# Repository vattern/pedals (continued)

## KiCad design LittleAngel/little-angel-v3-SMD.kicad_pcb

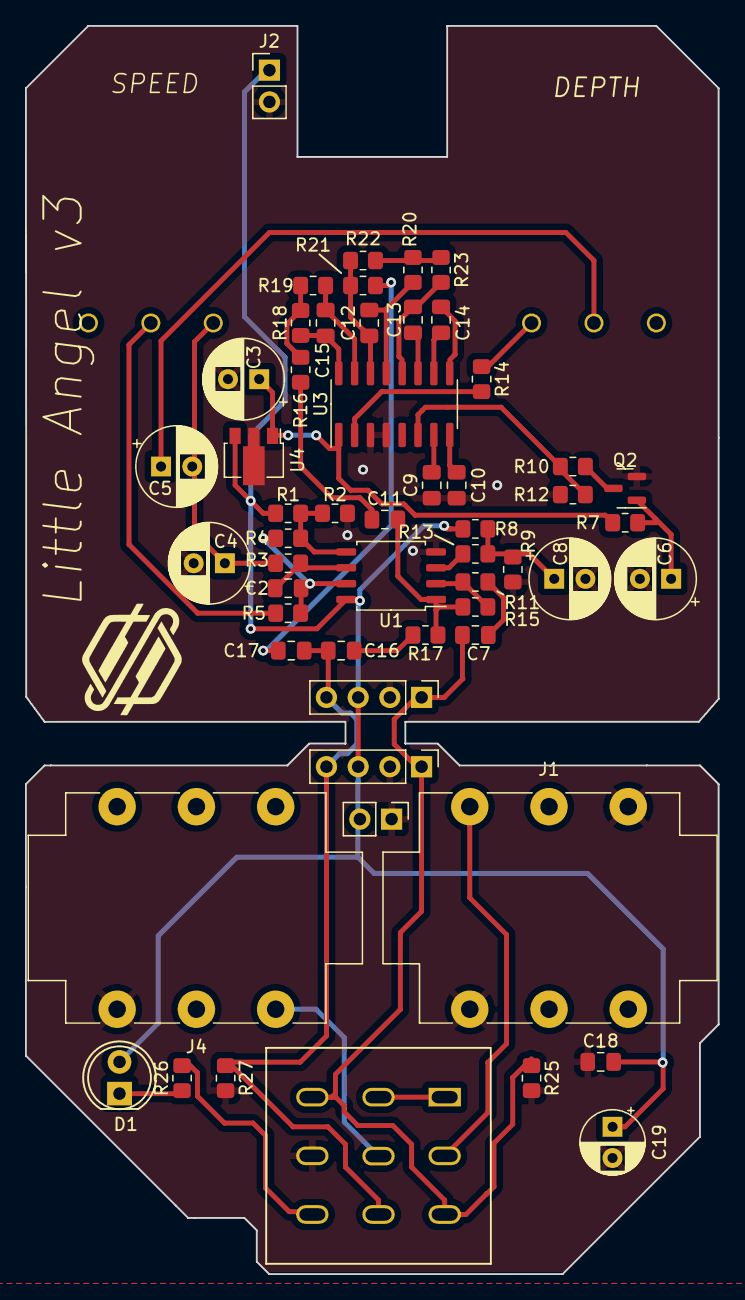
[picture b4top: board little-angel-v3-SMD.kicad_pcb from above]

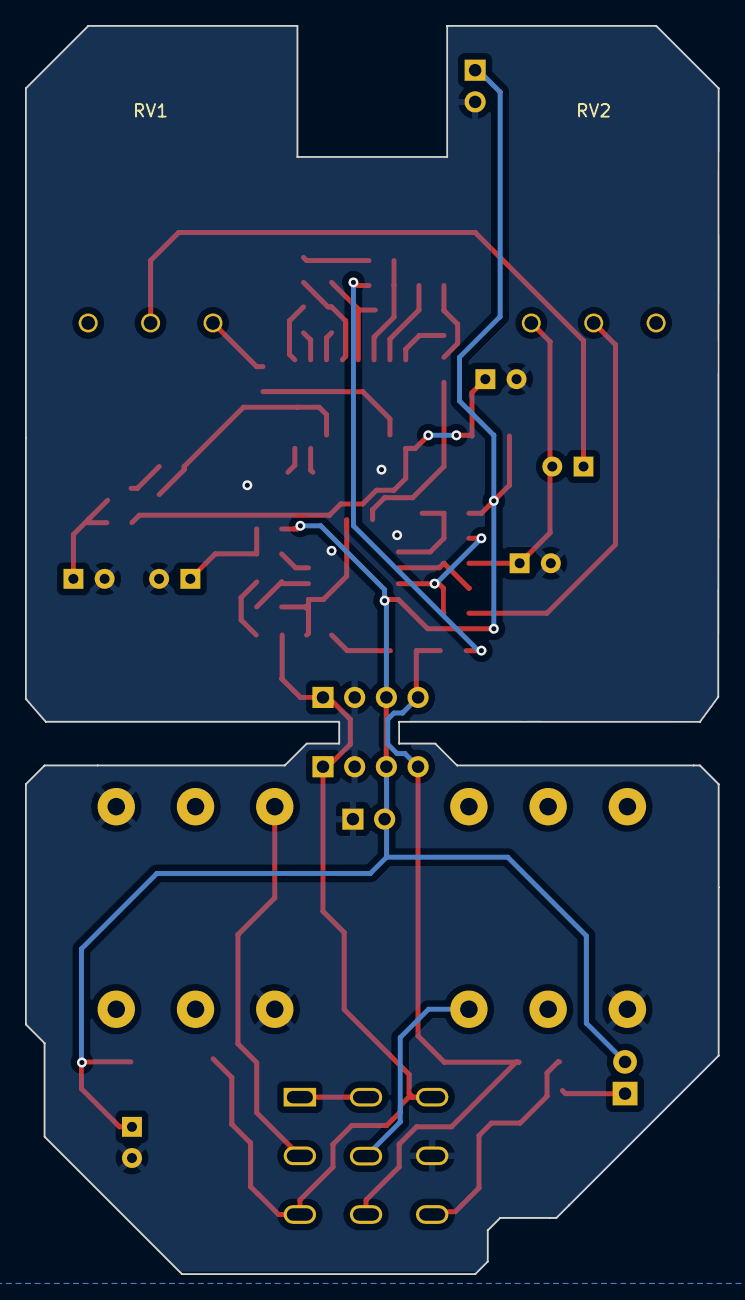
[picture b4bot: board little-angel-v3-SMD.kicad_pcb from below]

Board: 2 copper layers, 55.5 x 100.0 mm, 58 parts (2 on the bottom side), 41 nets.

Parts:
C2: 10nF; C_0805_2012Metric_Pad1.18x1.45mm_HandSolder
C3, C6, C8: 47uF; CP_Radial_D6.3mm_P2.50mm
C4, C5: 10uF; CP_Radial_D6.3mm_P2.50mm
C7, C9, C10, C11, C16, C17, C18: 100nF; C_0805_2012Metric_Pad1.18x1.45mm_HandSolder
C12: 10n; C_0805_2012Metric_Pad1.18x1.45mm_HandSolder
C13, C14: 100n; C_0805_2012Metric_Pad1.18x1.45mm_HandSolder
C15: 3n3; C_0805_2012Metric_Pad1.18x1.45mm_HandSolder
C19: 100uF; CP_Radial_D5.0mm_P2.50mm
D1: LED; LED-5MM
J1, J4: NMJ6HCD2; Jack_6.35mm_Neutrik_NMJ6HCD2_Horizontal
J2, J3: V+ GND; PinHeader_1x02_P2.54mm_Vertical
JOVGI1, JOVGI2: OVGI; Pin_Header_Straight_1x04_Pitch2.54mm
N1: Housing; 1590B
Q2: MMBT3904; SOT-23
R1: 100k; R_0805_2012Metric_Pad1.20x1.40mm_HandSolder
R2: 47k; R_0805_2012Metric_Pad1.20x1.40mm_HandSolder
R3: 220K; R_0805_2012Metric_Pad1.20x1.40mm_HandSolder
R4: 220k; R_0805_2012Metric_Pad1.20x1.40mm_HandSolder
R5: 4k7; R_0805_2012Metric_Pad1.20x1.40mm_HandSolder
R7: 68K; R_0805_2012Metric_Pad1.20x1.40mm_HandSolder
R8, R9, R16, R17, R18, R19, R20, R21, R22, R23: 10k; R_0805_2012Metric_Pad1.20x1.40mm_HandSolder
R10: 100R; R_0805_2012Metric_Pad1.20x1.40mm_HandSolder
R11: 470k; R_0805_2012Metric_Pad1.20x1.40mm_HandSolder
R12: 2k2; R_0805_2012Metric_Pad1.20x1.40mm_HandSolder
R13: 330k; R_0805_2012Metric_Pad1.20x1.40mm_HandSolder
R14: 33k; R_0805_2012Metric_Pad1.20x1.40mm_HandSolder
R15, R25: 1M; R_0805_2012Metric_Pad1.20x1.40mm_HandSolder
R26: 1K; R_0805_2012Metric_Pad1.20x1.40mm_HandSolder
R27: 100K; R_0805_2012Metric_Pad1.20x1.40mm_HandSolder
RV1: 470K lin; Potentiometer_ALPHA_RV16106N
RV2: 100k lin; Potentiometer_ALPHA_RV16106N
SW1: SW_3PDT; 3PDT-Footswitch
U1: NE5532; SOIC-8_5.275x5.275mm_P1.27mm
U3: PT2399; SOIC-16_3.9x9.9mm_P1.27mm
U4: MC78L05_SOT89; SOT-89-3

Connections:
+5V: C3.1, R7.2, U3.1 (VCC), U4.1 (OUT)
+9V: C18.2, C19.1, D1.2 (A), J2.1, J3.2, JOVGI1.3, JOVGI2.3, R1.2, R8.2, U1.8 (V+), U4.3 (IN)
GND: C3.2, C4.2, C6.2, C8.2, C9.1, C10.1, C18.1, C19.2, J1.S, J1.TN, J2.2, J3.1, J4.S, JOVGI1.2, JOVGI2.2, Q2.2 (E), R2.1, R9.1, R12.1, R25.2, R27.2, SW1.6 (B), U1.4 (V-), U3.3 (AGND), U3.4 (DGND), U4.2 (GND)
I: C7.1, JOVGI1.1, JOVGI2.1, R25.1, SW1.3 (A), SW1.7 (C)
unnamed: C2.2, R4.2, R5.1, U1.7
unnamed: C4.1, C5.2, R3.2, RV2.1
unnamed: C5.1, RV1.2
unnamed: C7.2, R11.1
unnamed: C8.1, R8.1, R9.2, R13.1
unnamed: C11.1, R16.1
unnamed: C11.2, R15.2, R17.1, U1.1
unnamed: C16.1, R17.2
unnamed: C17.1, R21.2
unnamed: D1.1 (K), R26.1
unnamed: C6.1, Q2.1 (B), R7.1
unnamed: Q2.3 (C), R10.1
unnamed: R5.2, RV2.2
unnamed: R14.1, RV1.3
unnamed: R16.2, R18.2, R19.2
unnamed: R20.1, R22.1, R23.1
unnamed: SW1.1 (A), SW1.2 (A)
unnamed: J1.T, SW1.4 (B)
unnamed: J4.T, SW1.5 (B)
unnamed: R26.2, SW1.9 (C)
unnamed: R13.2, U1.3 (+)
unnamed: R11.2, R15.1, U1.2 (-)
unnamed: R1.1, R2.2, R4.1, U1.5 (+)
unnamed: C2.1, R3.1, U1.6 (-)
unnamed: C10.2, U3.8 (CC0)
unnamed: C9.2, U3.7 (CC1)
unnamed: C15.1, R18.1, U3.16 (LPF1-IN)
unnamed: C15.2, R19.1, U3.15 (LPF1-OUT)
unnamed: C12.2, R20.2, U3.13 (LPF2-IN)
unnamed: C12.1, R21.1, R22.2, U3.14 (LPF2-OUT)
unnamed: C14.1, U3.10 (OP1-IN)
unnamed: C14.2, U3.9 (OP1-OUT)
unnamed: C13.2, U3.11 (OP2-IN)
unnamed: C13.1, R23.2, U3.12 (OP2-OUT)
unnamed: R14.2, U3.2 (REF)
unnamed: R10.2, R12.2, U3.6 (VCO)
O: C16.2, C17.2, JOVGI1.4, JOVGI2.4, R27.1, SW1.8 (C)

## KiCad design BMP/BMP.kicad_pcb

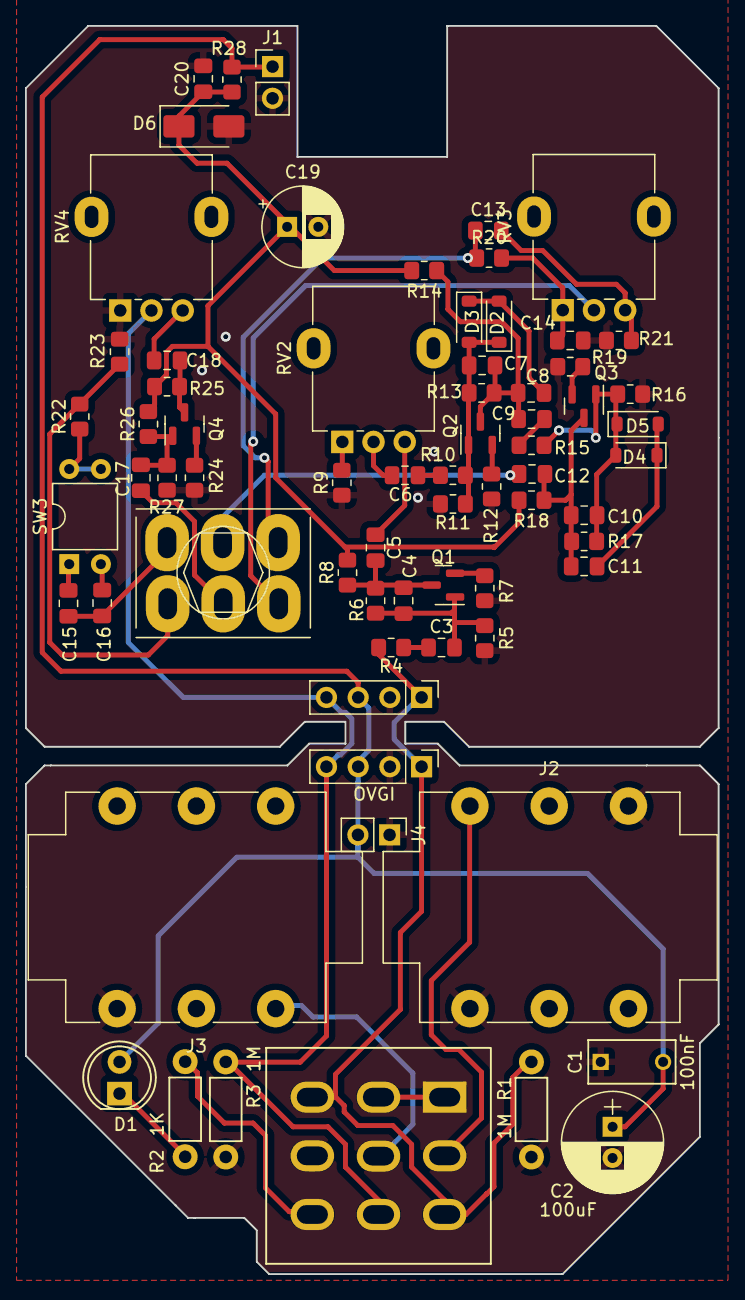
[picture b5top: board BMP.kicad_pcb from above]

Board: 2 copper layers, 55.5 x 100.0 mm, 71 parts (0 on the bottom side), 42 nets.

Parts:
C1: 100nF; C_Rect_L7_W3.5_P5
C2: 100uF; CP_Radial_D8.0mm_P2.50mm
C3, C5, C6, C8, C9, C11, C12, C17, C18, C20: 100n; C_0805_2012Metric_Pad1.18x1.45mm_HandSolder
C4, C7, C10: 470p; C_0805_2012Metric_Pad1.18x1.45mm_HandSolder
C13: 3n9; C_0805_2012Metric_Pad1.18x1.45mm_HandSolder
C14, C16: 10n; C_0805_2012Metric_Pad1.18x1.45mm_HandSolder
C15: 4n7; C_0805_2012Metric_Pad1.18x1.45mm_HandSolder
C19: 100u; CP_Radial_D6.3mm_P2.50mm
D1: LED; LED-5MM
D2, D3, D4, D5: 1N4148W; D_SOD-123
D6: US1G; D_SMA
J1, J4: V+ GND; PinHeader_1x02_P2.54mm_Vertical
J2, J3: NMJ6HCD2; Jack_6.35mm_Neutrik_NMJ6HCD2_Horizontal
JOVGI1, JOVGI2: OVGI; Pin_Header_Straight_1x04_Pitch2.54mm
N1: Housing; 1590B
Q1, Q2, Q3, Q4: BC849; SOT-23
R1, R3: 1M; Resistor_Horizontal_RM7mm
R2: 1K; Resistor_Horizontal_RM7mm
R4, R20, R21: 33k; R_0805_2012Metric_Pad1.20x1.40mm_HandSolder
R5, R11, R16, R27: 100k; R_0805_2012Metric_Pad1.20x1.40mm_HandSolder
R6, R13, R17, R26: 470k; R_0805_2012Metric_Pad1.20x1.40mm_HandSolder
R7, R12, R19, R28: 100R; R_0805_2012Metric_Pad1.20x1.40mm_HandSolder
R8, R14, R18, R25: 12k; R_0805_2012Metric_Pad1.20x1.40mm_HandSolder
R9: 560R; R_0805_2012Metric_Pad1.20x1.40mm_HandSolder
R10, R15: 8k2; R_0805_2012Metric_Pad1.20x1.40mm_HandSolder
R22, R23: 47k; R_0805_2012Metric_Pad1.20x1.40mm_HandSolder
R24: 2k7; R_0805_2012Metric_Pad1.20x1.40mm_HandSolder
RV2, RV3, RV4: 100kB; Potentiometer_Alpha_RD901F-40-00D_Single_Vertical
SW1: SW_3PDT; 3PDT-Footswitch
SW2: SW_DPDT_x2; SW_Toggle_Blue_wSlots_1
SW3: SW_DIP_x02; DIP-4_W7.62mm

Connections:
+9V: C1.2, C2.1, D1.2 (A), J1.1, J4.2, JOVGI1.3, JOVGI2.3, R28.1
A: C12.2, SW2.2 (B)
GND: C1.1, C2.2, C14.1, C19.2, C20.1, D6.2 (A), J1.2, J2.S, J2.TN, J3.S, J4.1, JOVGI1.2, JOVGI2.2, R1.2, R3.2, R5.1, R7.1, R9.1, R11.1, R12.1, R16.1, R19.1, R21.1, R23.1, R24.1, R27.1, RV4.1, SW1.6 (B)
I: JOVGI1.1, JOVGI2.1, R1.1, R4.1, SW1.3 (A), SW1.7 (C)
unnamed: C3.1, R4.2
unnamed: C5.2, RV2.3
unnamed: C6.1, RV2.2
unnamed: C6.2, R10.1
unnamed: C9.2, R15.1
unnamed: C13.2, R21.2, RV3.3
unnamed: C14.2, R20.2, RV3.1
unnamed: C15.2, SW3.1
unnamed: C16.2, SW3.2
unnamed: C18.1, RV4.3
unnamed: D1.1 (K), R2.1
unnamed: C8.1, D2.2 (A), D3.1 (K)
unnamed: C7.1, D2.1 (K), D3.2 (A), Q2.1 (B), R10.2, R11.2, R13.1
unnamed: C10.1, D4.2 (A), D5.1 (K), Q3.1 (B), R15.2, R16.2, R17.1
unnamed: C11.1, D4.1 (K), D5.2 (A)
unnamed: C3.2, C4.1, Q1.1 (B), R5.2, R6.1
unnamed: C4.2, C5.1, Q1.3 (C), R6.2, R8.1
unnamed: Q1.2 (E), R7.2
unnamed: C7.2, C8.2, C9.1, Q2.3 (C), R13.2, R14.1
unnamed: Q2.2 (E), R12.2
unnamed: C10.2, C11.2, C12.1, Q3.3 (C), R17.2, R18.1
unnamed: Q3.2 (E), R19.2
unnamed: C17.1, Q4.1 (B), R26.1, R27.2
unnamed: C18.2, Q4.3 (C), R25.1
unnamed: Q4.2 (E), R24.2
unnamed: R9.2, RV2.1
unnamed: R22.1, SW3.3, SW3.4
unnamed: SW1.1 (A), SW1.2 (A)
unnamed: J2.T, SW1.4 (B)
unnamed: J3.T, SW1.5 (B)
unnamed: R2.2, SW1.9 (C)
unnamed: C15.1, C16.1, SW2.1 (A)
unnamed: C13.1, R20.1, SW2.3 (C)
unnamed: R22.2, R23.2, SW2.4 (A)
unnamed: C17.2, SW2.5 (B)
unnamed: RV3.2, SW2.6 (C)
O: JOVGI1.4, JOVGI2.4, R3.1, RV4.2, SW1.8 (C)
VP: C19.1, C20.2, D6.1 (K), R8.2, R14.2, R18.2, R25.2, R26.2, R28.2

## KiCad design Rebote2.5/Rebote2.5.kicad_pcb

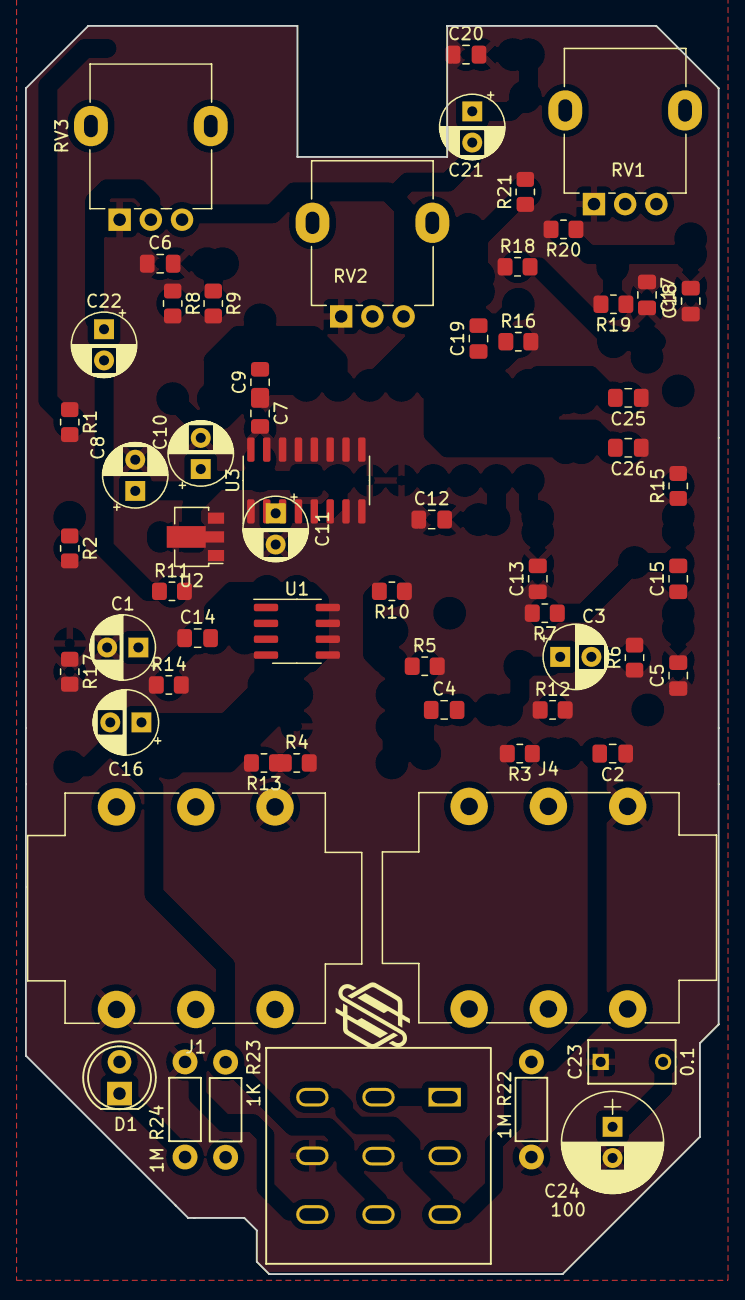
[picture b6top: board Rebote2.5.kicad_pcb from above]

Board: 2 copper layers, 55.5 x 100.0 mm, 61 parts (0 on the bottom side), 42 nets, no tracks yet.

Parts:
C1, C8, C10, C11: 47uF; CP_Radial_D5.0mm_P2.50mm
C2: 8n2; C_0805_2012Metric_Pad1.18x1.45mm_HandSolder
C3, C16, C21, C22: 1uF; CP_Radial_D5.0mm_P2.50mm
C4: 5pF; C_0805_2012Metric_Pad1.18x1.45mm_HandSolder
C5: 27nF; C_0805_2012Metric_Pad1.18x1.45mm_HandSolder
C6, C17, C18: 10nF; C_0805_2012Metric_Pad1.18x1.45mm_HandSolder
C7, C12, C13, C15, C20: 100nF; C_0805_2012Metric_Pad1.18x1.45mm_HandSolder
C9: 560pF; C_0805_2012Metric_Pad1.18x1.45mm_HandSolder
C14: 51pF; C_0805_2012Metric_Pad1.18x1.45mm_HandSolder
C19: 1nF; C_0805_2012Metric_Pad1.18x1.45mm_HandSolder
C23: 0.1; C_Rect_L7_W3.5_P5
C24: 100; CP_Radial_D8.0mm_P2.50mm
C25, C26: 82nF; C_0805_2012Metric_Pad1.18x1.45mm_HandSolder
D1: LED; LED-5MM
J1, J4: NMJ6HCD2; Jack_6.35mm_Neutrik_NMJ6HCD2_Horizontal
N1: Housing; 1590B
R1, R2, R6, R7, R8, R16, R18, R19: 12K; R_0805_2012Metric_Pad1.20x1.40mm_HandSolder
R3, R4, R5: 510K; R_0805_2012Metric_Pad1.20x1.40mm_HandSolder
R9: 47K; R_0805_2012Metric_Pad1.20x1.40mm_HandSolder
R10, R14, R20: 24K; R_0805_2012Metric_Pad1.20x1.40mm_HandSolder
R11: 33K; R_0805_2012Metric_Pad1.20x1.40mm_HandSolder
R12, R13: 1k; R_0805_2012Metric_Pad1.20x1.40mm_HandSolder
R15: 15K; R_0805_2012Metric_Pad1.20x1.40mm_HandSolder
R17: 100K; R_0805_2012Metric_Pad1.20x1.40mm_HandSolder
R21: 2k7; R_0805_2012Metric_Pad1.20x1.40mm_HandSolder
R22, R24: 1M; Resistor_Horizontal_RM7mm
R23: 1K; Resistor_Horizontal_RM7mm
RV1: 50KB; Potentiometer_Alpha_RD901F-40-00D_Single_Vertical
RV2: 25KB; Potentiometer_Alpha_RD901F-40-00D_Single_Vertical
RV3: 100KB; Potentiometer_Alpha_RD901F-40-00D_Single_Vertical
SW1: SW_3PDT; 3PDT-Footswitch
U1: TL072; SOIC-8_3.9x4.9mm_P1.27mm
U2: L78L05_SOT89; SOT-89-3
U3: PT2399; SOIC-16_3.9x9.9mm_P1.27mm

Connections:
+5V: C7.2, C8.1, C10.1, U2.1 (OUT), U3.1 (VCC)
+9V: C23.2, C24.1, D1.2 (A), R1.1, U1.8 (V+), U2.3 (IN)
AI: C3.1, C4.2, R5.2, R10.1, U1.7
DELAY_OUT: C26.2, R16.1, U3.12 (OP2-OUT)
GND: C1.2, C5.1, C6.1, C7.1, C8.2, C10.2, C11.2, C12.1, C13.1, C17.1, C18.1, C20.1, C23.1, C24.2, J1.S, J1.TN, J4.S, R2.2, R17.1, R22.2, R24.2, RV1.1, RV2.1, RV3.1, SW1.6 (B), U1.4 (V-), U2.2 (GND), U3.3 (AGND), U3.4 (DGND)
I: C2.1, R22.1, SW1.3 (A), SW1.7 (C)
LPF1-IN: C9.1, R8.2, U3.16 (LPF1-IN)
LPF1-OUT: C9.2, R9.2, U3.15 (LPF1-OUT)
LPF2-IN: C19.1, R19.2, U3.13 (LPF2-IN)
LPF2-OUT: C19.2, R20.2, R21.1, U3.14 (LPF2-OUT)
unnamed: C2.2, R3.1
unnamed: C3.2, R6.1
unnamed: C6.2, R7.2, R8.1, R9.1
unnamed: C14.2, C16.1, R14.2, U1.1
unnamed: C5.2, C15.1, R6.2, R7.1
unnamed: C15.2, R15.1
unnamed: C17.2, R16.2, R18.1
unnamed: C18.2, R18.2, R19.1, R20.1
unnamed: C20.2, C21.1, R21.2
unnamed: C21.2, RV2.3, RV3.3
unnamed: C22.1, RV3.2
unnamed: C22.2, R11.1
unnamed: D1.1 (K), R23.1
unnamed: R12.2, RV1.2, RV1.3
unnamed: R15.2, RV2.2
unnamed: SW1.1 (A), SW1.2 (A)
unnamed: J1.T, SW1.4 (B)
unnamed: J4.T, SW1.5 (B)
unnamed: R23.2, SW1.9 (C)
unnamed: R13.2, U1.3 (+)
unnamed: C14.1, R10.2, R11.2, R14.1, U1.2 (-)
unnamed: R4.2, U1.5 (+)
unnamed: C4.1, R3.2, R5.1, U1.6 (-)
unnamed: C13.2, U3.8 (CC0)
unnamed: C12.2, U3.7 (CC1)
unnamed: C25.2, U3.10 (OP1-IN)
unnamed: C25.1, U3.9 (OP1-OUT)
unnamed: C26.1, U3.11 (OP2-IN)
unnamed: C11.1, U3.2 (REF)
unnamed: R12.1, U3.6 (VCO)
O: C16.2, R17.2, R24.1, SW1.8 (C)
VD: C1.1, R1.2, R2.1, R4.1, R13.1

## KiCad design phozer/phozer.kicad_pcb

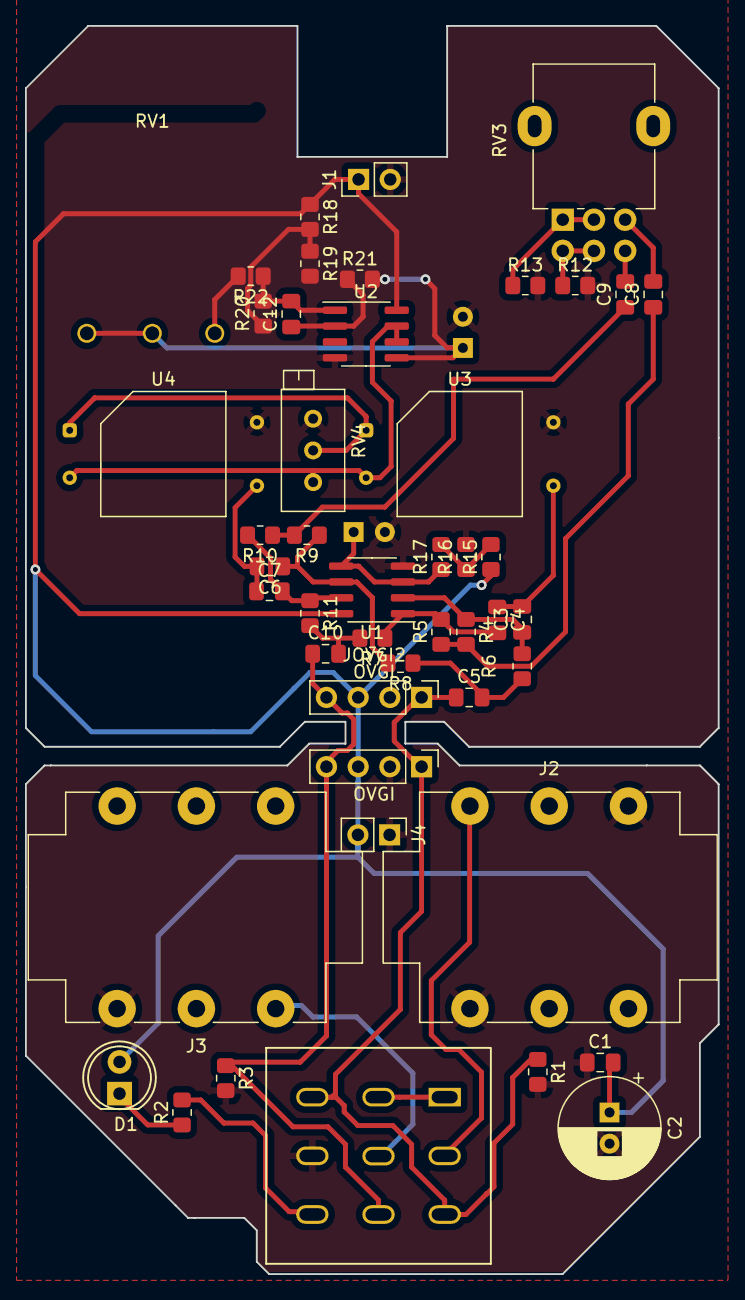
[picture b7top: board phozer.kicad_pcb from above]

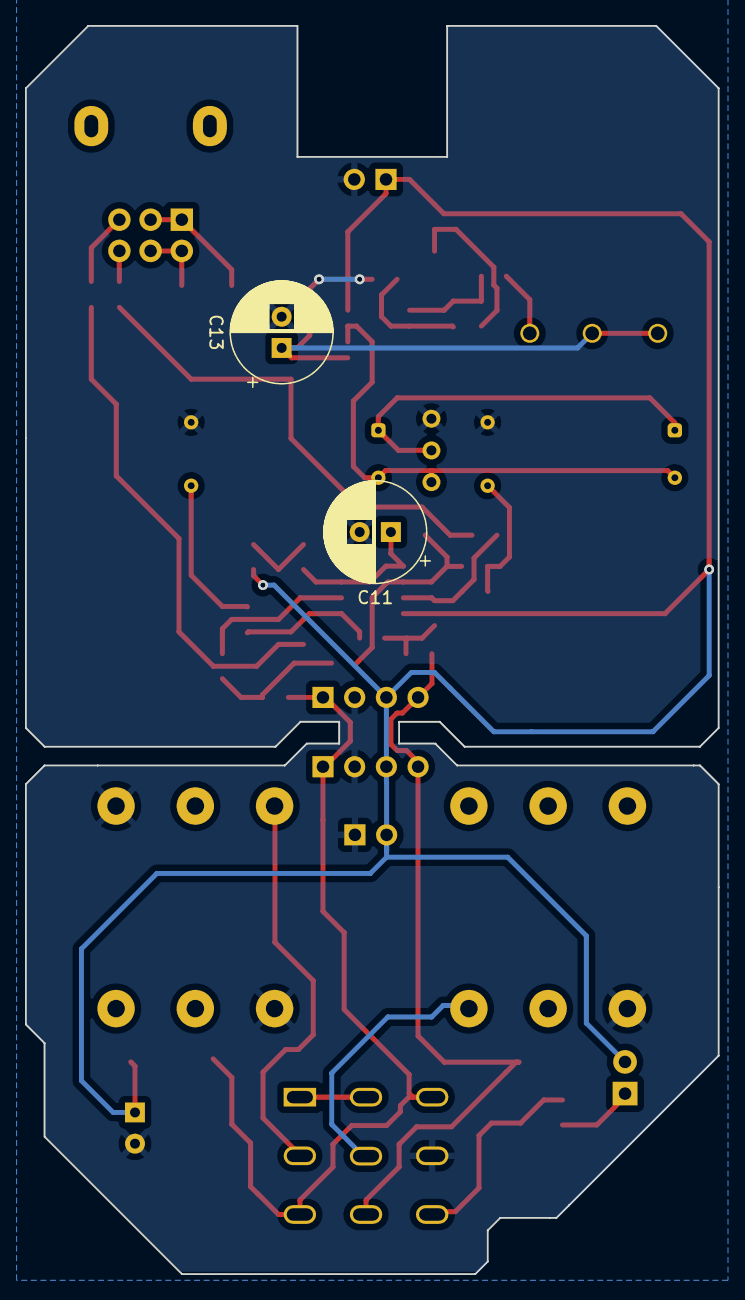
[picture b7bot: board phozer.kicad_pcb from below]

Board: 2 copper layers, 55.5 x 100.0 mm, 50 parts (2 on the bottom side), 32 nets.

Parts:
C1: 100nF; C_0805_2012Metric_Pad1.18x1.45mm_HandSolder
C2: 100uF; CP_Radial_D8.0mm_P2.50mm
C3, C4, C9, C12: 10n; C_0805_2012Metric_Pad1.18x1.45mm_HandSolder
C5, C6, C7: 2n2; C_0805_2012Metric_Pad1.18x1.45mm_HandSolder
C8, C10: 100n; C_0805_2012Metric_Pad1.18x1.45mm_HandSolder
C11, C13: 220u; CP_Radial_D8.0mm_P2.50mm
D1: LED; LED-5MM
J1, J4: V+ GND; PinHeader_1x02_P2.54mm_Vertical
J2, J3: NMJ6HCD2; Jack_6.35mm_Neutrik_NMJ6HCD2_Horizontal
JOVGI1, JOVGI2: OVGI; Pin_Header_Straight_1x04_Pitch2.54mm
N1: Housing; 1590B
R1, R3: 1M; R_0805_2012Metric_Pad1.20x1.40mm_HandSolder
R2: 1K; R_0805_2012Metric_Pad1.20x1.40mm_HandSolder
R4, R5, R9, R10: 75k; R_0805_2012Metric_Pad1.20x1.40mm_HandSolder
R6, R8, R18, R19, R20, R21: 150k; R_0805_2012Metric_Pad1.20x1.40mm_HandSolder
R7, R11, R15, R16: 27k; R_0805_2012Metric_Pad1.20x1.40mm_HandSolder
R12, R13: 39k; R_0805_2012Metric_Pad1.20x1.40mm_HandSolder
R17: 220; R_0805_2012Metric_Pad1.20x1.40mm_HandSolder
R22: 6k8; R_0805_2012Metric_Pad1.20x1.40mm_HandSolder
RV1: ALPHA-16mm; Potentiometer_ALPHA_RV16106N
RV3: 100k Lin; Potentiometer_Alpha_RD902F-40-00D_Dual_Vertical
RV4: R_Potentiometer_Trim; Potentiometer_Bourns_3296X_Horizontal
SW1: SW_3PDT; 3PDT-Footswitch
U1, U2: TL072; SOIC-8_3.9x4.9mm_P1.27mm
U3, U4: VTL5C; PerkinElmer_VTL5C

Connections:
+9V: C1.2, C2.1, D1.2 (A), J1.1, J4.2, JOVGI1.3, JOVGI2.3, R15.1, R18.1, U1.8 (V+), U2.8 (V+)
A: C3.2, C4.1, U3.4
B: C6.2, C7.1, U4.4
GND: C1.1, C2.2, C11.2, C13.2, J1.2, J2.S, J2.TN, J3.S, J4.1, JOVGI1.2, JOVGI2.2, R1.2, R3.2, R12.2, R13.2, R16.2, R19.2, RV4.3, SW1.6 (B), U1.4 (V-), U2.4 (V-), U3.3, U4.3
I: C5.1, JOVGI1.1, JOVGI2.1, R1.1, SW1.3 (A), SW1.7 (C)
unnamed: C4.2, R5.2, R7.1, U1.1
unnamed: C5.2, R6.1, R8.1
unnamed: C7.2, R10.2, R11.1, U1.7
unnamed: C8.1, R4.2, R5.1
unnamed: C8.2, RV3.3
unnamed: C9.1, R9.2, R10.1
unnamed: C9.2, RV3.6
unnamed: C10.2, R7.2, R11.2
unnamed: C12.2, R20.2, R22.1, U2.1
unnamed: D1.1 (K), R2.1
unnamed: R12.1, RV3.4, RV3.5
unnamed: R13.1, RV3.1, RV3.2
unnamed: R15.2, R16.1, R17.2
unnamed: R22.2, RV1.3
unnamed: SW1.1 (A), SW1.2 (A)
unnamed: J2.T, SW1.4 (B)
unnamed: J3.T, SW1.5 (B)
unnamed: R2.2, SW1.9 (C)
unnamed: C3.1, R4.1, R6.2, U1.2 (-)
unnamed: C6.1, R8.2, R9.1, U1.6 (-)
unnamed: R18.2, R19.1, R20.1, U2.3 (+)
unnamed: C12.1, R21.1, U2.2 (-)
unnamed: C13.1, R21.2, RV1.1, RV1.2, U2.5 (+)
unnamed: RV4.1, U2.6 (-), U2.7, U3.2 (+), U4.2 (+)
unnamed: RV4.2, U3.1 (-), U4.1 (-)
O: C10.1, JOVGI1.4, JOVGI2.4, R3.1, SW1.8 (C)
VB: C11.1, R17.1, U1.3 (+), U1.5 (+)

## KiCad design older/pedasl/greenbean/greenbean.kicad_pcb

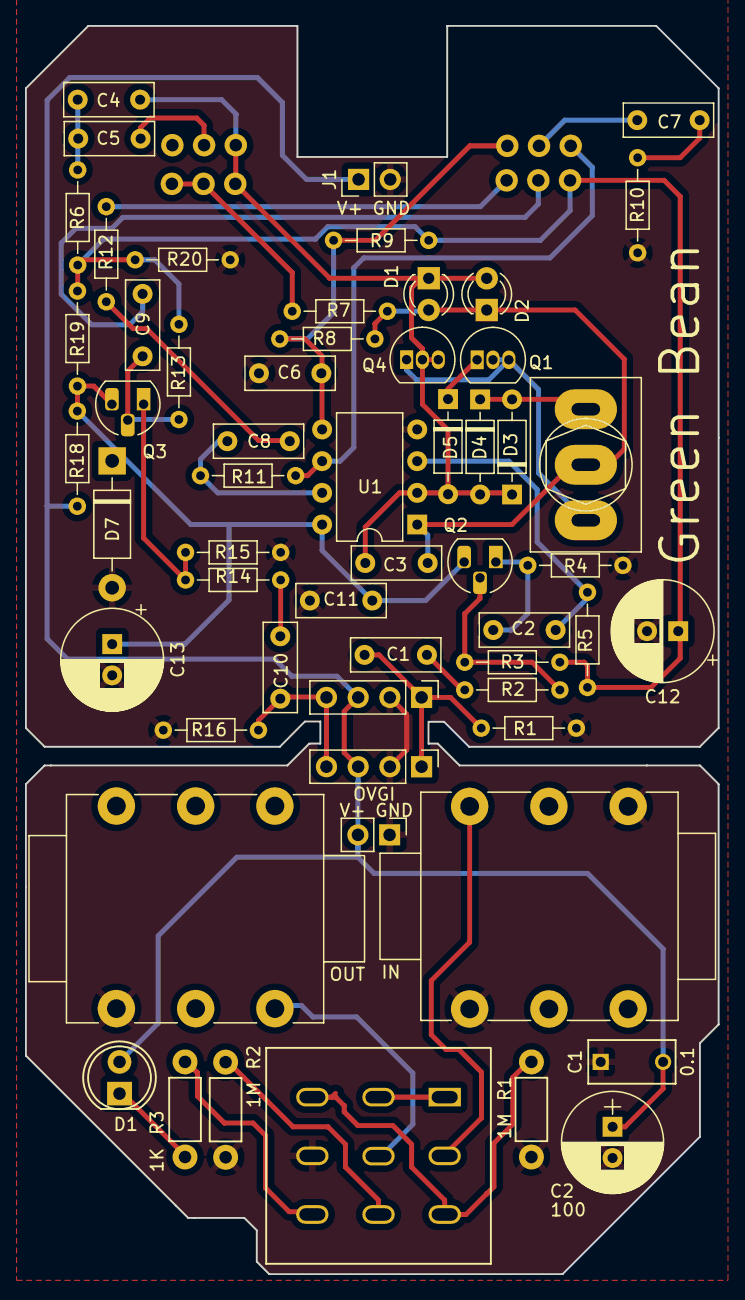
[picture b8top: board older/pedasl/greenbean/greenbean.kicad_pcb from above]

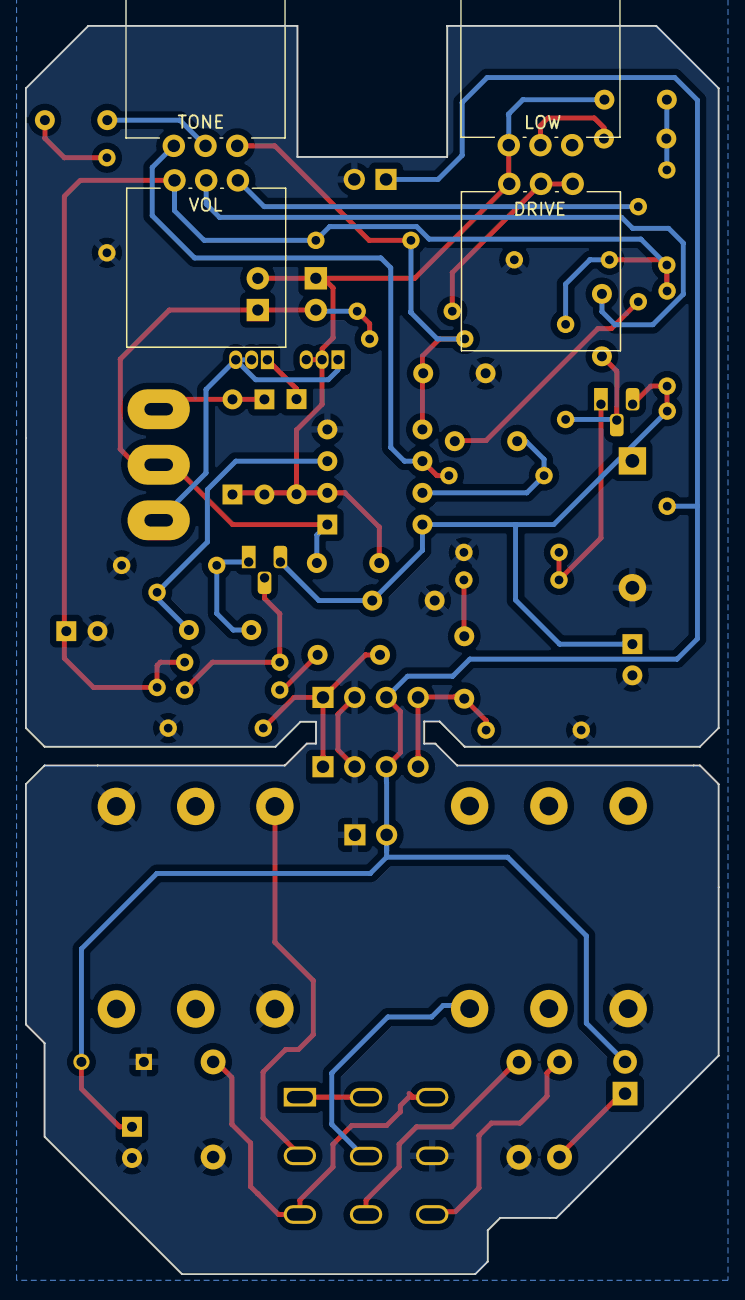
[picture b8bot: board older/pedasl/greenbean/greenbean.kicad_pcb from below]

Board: 2 copper layers, 55.5 x 100.0 mm, 61 parts (4 on the bottom side), 36 nets.

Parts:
C1: 0.1; C_Rect_L7_W3.5_P5
C1#2: 20n; C_Disc_D7.0mm_W2.5mm_P5.00mm
C2, C8, C10: 1u; C_Disc_D7.0mm_W2.5mm_P5.00mm
C2#2: 100; CP_Radial_D8.0mm_P2.50mm
C3: 51p; C_Disc_D7.0mm_W2.5mm_P5.00mm
C4: 47n; C_Disc_D7.0mm_W2.5mm_P5.00mm
C5: 150n; C_Disc_D7.0mm_W2.5mm_P5.00mm
C6, C7, C11: 220n; C_Disc_D7.0mm_W2.5mm_P5.00mm
C9: 100n; C_Disc_D7.0mm_W2.5mm_P5.00mm
C12, C13: C_Polarized; CP_Radial_D8.0mm_P2.50mm
D1, D2: LED; LED_D3.0mm
D1#2: LED; LED-5MM
D3, D4: 1N914; D_DO-35_SOD27_P7.62mm_Horizontal
D5: BAT41; D_DO-35_SOD27_P7.62mm_Horizontal
D7: 1N4001; D_DO-41_SOD81_P10.16mm_Horizontal
DRIVE: 500KA; Potentiometer_Vishay_148-149_Single_Vertical
J1, J4: V+ GND; Pin_Header_Straight_1x02_Pitch2.54mm
J2: IN; NMJ6HCD2
J3: OUT; NMJ6HCD2
JOVGI1, JOVGI2: OVGI; Pin_Header_Straight_1x04_Pitch2.54mm
LOW: 20KB; Potentiometer_Vishay_148-149_Single_Vertical
Q1, Q4: 2N7000; TO-92_Inline
Q2, Q3: Q_NPN_EBC; TO-92L_HandSolder
R1: 1M; R_Axial_DIN0204_L3.6mm_D1.6mm_P7.62mm_Horizontal
R1#2, R2#2: 1M; Resistor_Horizontal_RM7mm
R2, R8, R11, R12: 1k; R_Axial_DIN0204_L3.6mm_D1.6mm_P7.62mm_Horizontal
R3, R13: 510k; R_Axial_DIN0204_L3.6mm_D1.6mm_P7.62mm_Horizontal
R3#2: 1K; Resistor_Horizontal_RM7mm
R4, R5, R9, R14, R16, R19, R20: 10k; R_Axial_DIN0204_L3.6mm_D1.6mm_P7.62mm_Horizontal
R6: 4k7; R_Axial_DIN0204_L3.6mm_D1.6mm_P7.62mm_Horizontal
R7: 51k; R_Axial_DIN0204_L3.6mm_D1.6mm_P7.62mm_Horizontal
R10: 220R; R_Axial_DIN0204_L3.6mm_D1.6mm_P7.62mm_Horizontal
R15: 100R; R_Axial_DIN0204_L3.6mm_D1.6mm_P7.62mm_Horizontal
R18: 47R; R_Axial_DIN0204_L3.6mm_D1.6mm_P7.62mm_Horizontal
SW1: SW_3PDT; 3PDT-Footswitch
SW1#2: SW_SPDT; SW_Toggle_Blue_wSlots
TONE: 20KB; Potentiometer_Vishay_148-149_Single_Vertical
U1: RC4558; DIP-8_W7.62mm
VOL: 100KB; Potentiometer_Vishay_148-149_Single_Vertical

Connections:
+9V: C1.2, C2#2.1, D1#2.2, J1.1, J4.2, JOVGI1.3, JOVGI2.3, R18.2
/I: R1#2.1, SW1.3, SW1.7
/O: R2#2.1, SW1.8
A: C3.1, C4.2, D1.1 (K), D2.2 (A), D3.1 (K), D4.2 (A), D5.2 (A), DRIVE.1, LOW.3, Q4.2 (G), Q4.3 (D), U1.2 (-)
B: C3.2, D1.2 (A), D2.1 (K), R7.2, R8.1, SW1#2.2 (B), U1.1
GND: C1.1, C2#2.2, C6.1, C11.1, C12.2, C13.2, D7.2 (A), J1.2, J2.1, J2.5, J3.1, J4.1, JOVGI1.2, JOVGI2.2, R1.1, R1#2.2, R2#2.2, R4.1, R10.1, R14.1, R16.1, R20.1, SW1.6, U1.4 (V-)
unnamed: C1#2.2, R2.2
unnamed: C4.1, C5.1, R6.2
unnamed: C5.2, LOW.2
unnamed: C7.1, R10.2
unnamed: C7.2, TONE.2
unnamed: C8.1, R11.2, U1.7
unnamed: C8.2, R12.1
unnamed: C9.1, VOL.2
unnamed: C10.1, R15.2
unnamed: D1#2.1, R3#2.1
unnamed: D3.2 (A), D4.1 (K), SW1#2.1 (A)
unnamed: D5.1 (K), Q1.1 (S)
unnamed: DRIVE.2, DRIVE.3, R7.1
unnamed: J2.2, SW1.4
unnamed: J3.2, SW1.5
unnamed: Q1.2 (G), Q1.3 (D), Q4.1 (S), SW1#2.3 (C)
unnamed: Q2.2 (B), R2.1, R3.1
unnamed: C2.1, Q2.1 (E), R4.2
unnamed: C9.2, Q3.2 (B), R13.1
unnamed: Q3.1 (E), R14.2, R15.1
unnamed: R3#2.2, SW1.9
unnamed: R12.2, VOL.3
unnamed: SW1.1, SW1.2
unnamed: C2.2, R5.1, U1.3 (+)
unnamed: C6.2, R8.2, R9.1, TONE.1, U1.5 (+)
unnamed: R11.1, TONE.3, U1.6 (-)
VB: C12.1, R3.2, R5.2, R6.1, R9.2, R13.2, R19.1, R20.2, VOL.1
VC: C11.2, C13.1, D7.1 (K), Q2.3 (C), Q3.3 (C), R18.1, R19.2, U1.8 (V+)
/I: C1#2.1, JOVGI1.1, JOVGI2.1, R1.2
/O: C10.2, JOVGI1.4, JOVGI2.4, R16.2

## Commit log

2023-05-26 Add 1590B template project
2023-05-26 Add LittleAngel Birthday edition
2023-05-26 Add older designs pending revision
2023-05-26 Update LAC and GB old
2023-05-26 Add toggle 3d
2023-05-26 Move DOD280C to main
2023-05-26 Adding dod280c
2023-05-26 Move Rebote to main
2023-08-08 Add workflow yaml
2023-08-08 Test udate
